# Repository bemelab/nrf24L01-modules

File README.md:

# nRF24L01+ modülleri — Elfatek

nRF24L01+ tabanlı RF modül tasarımları. Her proje kendi klasöründe, kendi README'si ve tasarım notlarıyla durur.

| Proje | Klasör | İçerik |
|---|---|---|
| **nRF24L01+ PA/LNA modülleri** | [`nrf24-pa-module/`](nrf24-pa-module) | 19 mm genişlikte, standart 2×4 pin dizilimli kartlar: NRF24PA, NRF24PL (RFX2401C PA/LNA), NRF24DN (PA'sız), NRF24DP (PA'lı, regülatörlü) |

Tasarımlar KiCad 9 ile, tablolardan Python betikleriyle üretilir. **Kartlar henüz test edilmedi.**

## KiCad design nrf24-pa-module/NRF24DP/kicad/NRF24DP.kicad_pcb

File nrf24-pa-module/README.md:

# nRF24L01+ PA/LNA modülleri — Elfatek

19 × 34 mm, 4 katmanlı, standart nRF24L01 2×4 pin dizilimli nRF24L01+ + RFX2401C PA/LNA modülleri.
Chip anten (Johanson 2450AT18A100E) ya da U.FL, montajda 0 Ω ile seçilir.

| Kart | Klasör | Harmonik filtre |
|---|---|---|
| **NRF24PA** rev A | kök (`docs/`, `kicad/`, `tools/`, `uretim/`) | Ayrık pi LC (C15–C19, L4, L5) |
| **NRF24PL** rev A | [`NRF24PL/`](NRF24PL) | Hazır seramik LPF, Johanson 2450LP14A100E (FL1) |
| **NRF24DN** rev A | [`NRF24DN/`](NRF24DN) | PA'sız minimal modül, hazır balun-filtre + AMS1117-3.3, 19 × 26 mm |
| **NRF24DP** rev A | [`NRF24DP/`](NRF24DP) | Hazır balun-filtre + LPF + AMS1117-3.3, 19 × 31.75 mm |

Ayrıntılar: [NRF24PA](docs/Tasarim%20notlari.md) · [NRF24PL](NRF24PL/docs/Tasarim%20notlari.md) ·
[NRF24DN](NRF24DN/docs/Tasarim%20notlari.md) · [NRF24DP](NRF24DP/docs/Tasarim%20notlari.md) tasarım notları

## Durum

ERC / DRC temiz, üretim dosyaları hazır. **Kartta henüz test edilmedi**: anten eşleştirme, harmonik
spektrumu ve kristal frekansı ölçülmeli (tasarım notlarında "Kartta doğrulanması gerekenler").

## Yeniden üretim

Şema ve PCB `tools/parts.py` (parça / net / konum) ve `tools/routes.py` (yollar) tablolarından üretilir.
KiCad 9 gerekir (`tools/build.py` içindeki yollar).

```
python tools/build.py            # NRF24PA
python NRF24PL/tools/build.py    # NRF24PL
python NRF24DN/tools/build.py    # NRF24DN
python NRF24DP/tools/build.py    # NRF24DP
```

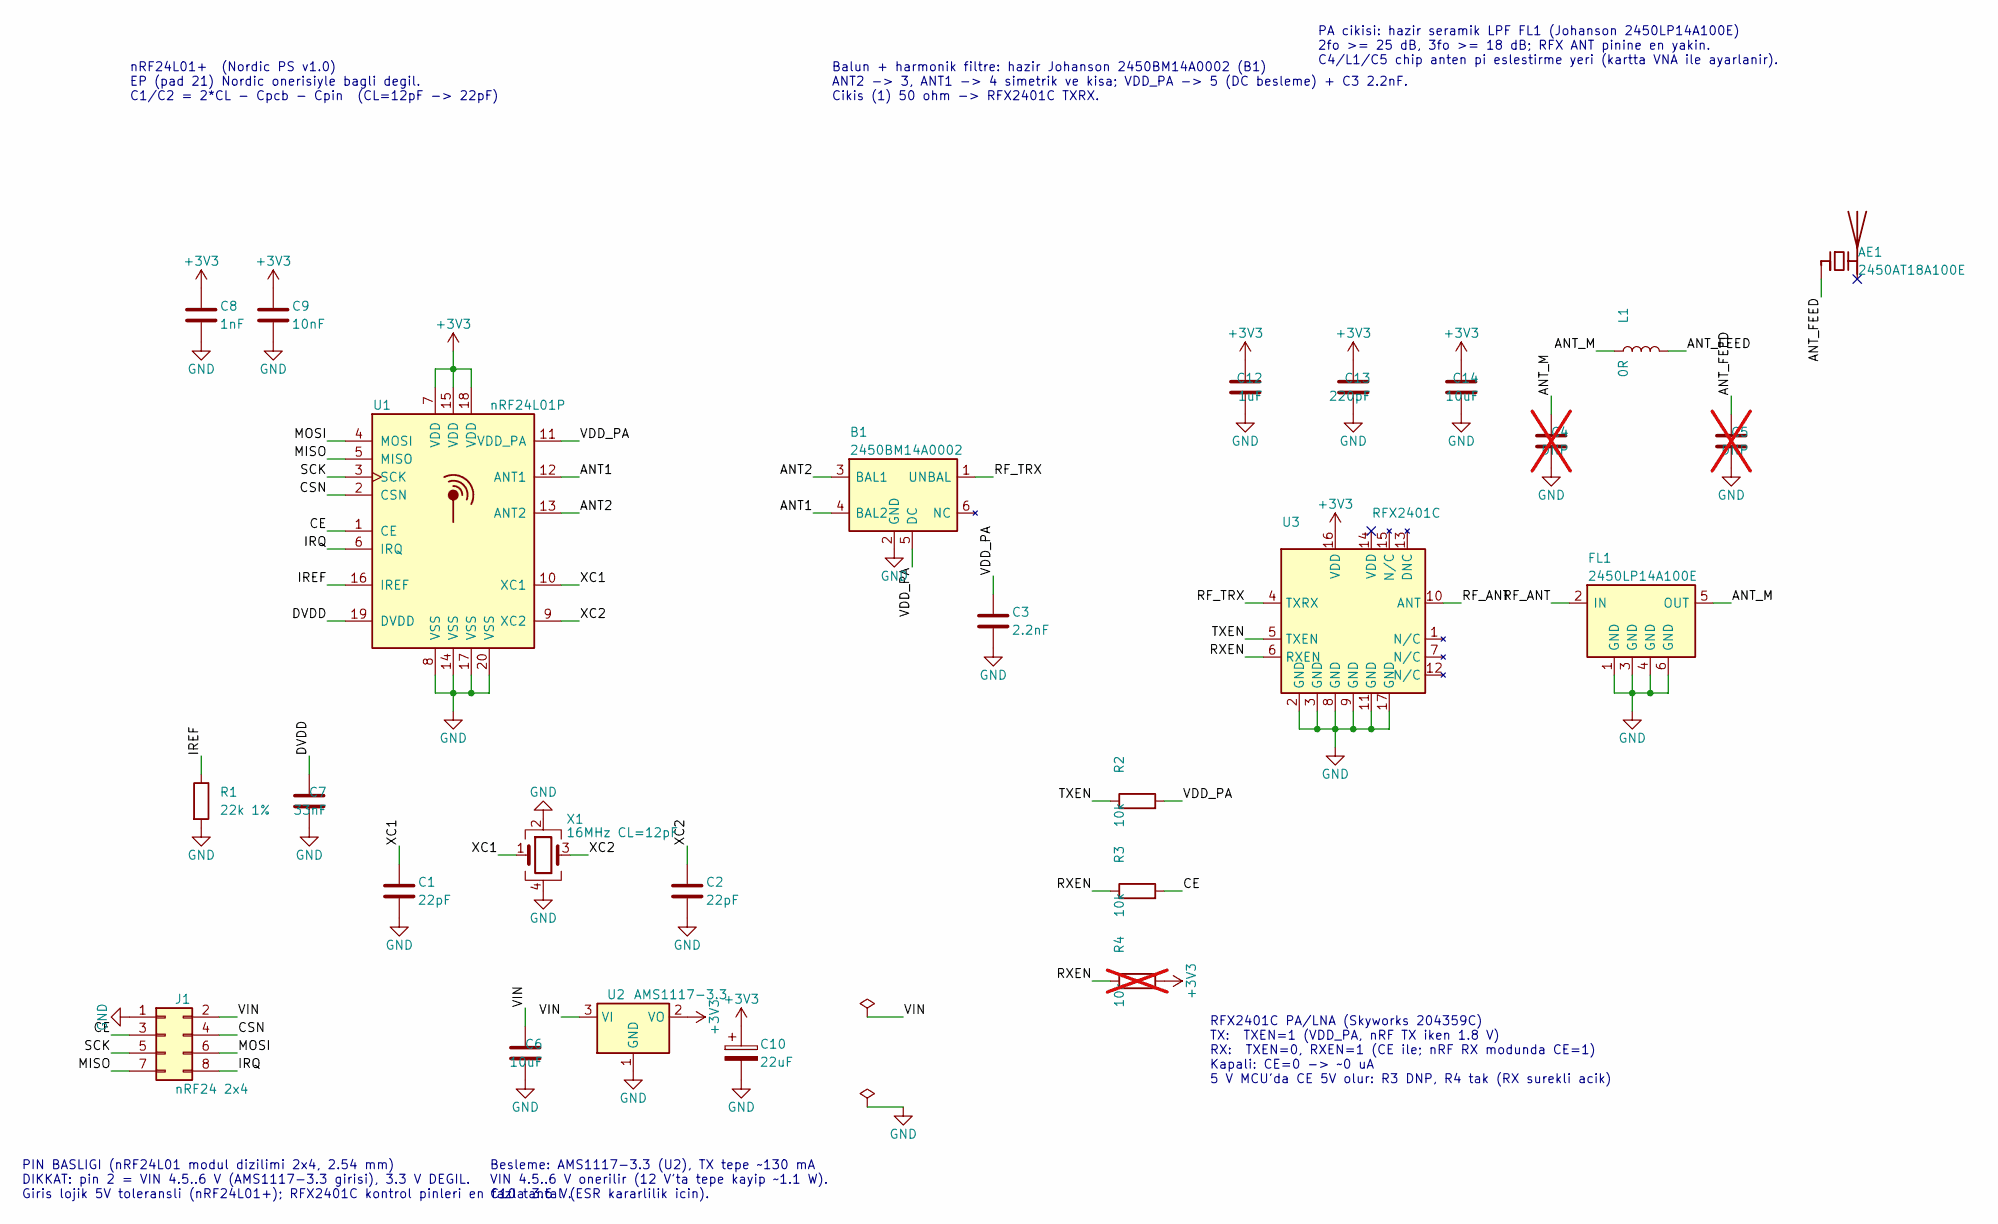
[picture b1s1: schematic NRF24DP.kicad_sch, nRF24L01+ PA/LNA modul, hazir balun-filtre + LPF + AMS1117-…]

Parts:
AE1: 2450AT18A100E; Johanson_2450AT18x100; MPN Johanson 2450AT18A100E
B1: 2450BM14A0002; Johanson_2450BM14_1.6x0.8mm; MPN Johanson 2450BM14A0002001T
C1, C2: 22pF; C_0402_1005Metric; MPN NP0 50V
C3: 2.2nF; C_0402_1005Metric; MPN X7R
C4, C5: DNP; C_0402_1005Metric; not fitted
C6: 10uF; C_0805_2012Metric; MPN X5R 25V
C7: 33nF; C_0402_1005Metric; MPN X7R
C8: 1nF; C_0402_1005Metric; MPN X7R
C9: 10nF; C_0402_1005Metric; MPN X7R
C10: 22uF; CP_EIA-3216-18_Kemet-A; MPN Tantal 22uF 10V A kilif
C12: 1uF; C_0402_1005Metric; MPN X5R 10V
C13: 220pF; C_0402_1005Metric; MPN NP0
C14: 10uF; C_0603_1608Metric; MPN X5R 10V
FL1: 2450LP14A100E; Johanson_2450LP14_1.6x0.8mm; MPN Johanson 2450LP14A100E
J1: nRF24 2x4; PinHeader_2x04_P2.54mm_Vertical
L1: 0R; L_0402_1005Metric
R1: 22k 1%; R_0402_1005Metric
R2, R3: 10k; R_0402_1005Metric
R4: 10k; R_0402_1005Metric; not fitted
U1: nRF24L01P; QFN-20-1EP_4x4mm_P0.5mm_EP2.5x2.5mm; MPN nRF24L01P-R
U2: AMS1117-3.3; SOT-223-3_TabPin2; MPN AMS1117-3.3 (AMS) / esdegeri
U3: RFX2401C; QFN-16-1EP_3x3mm_P0.5mm_EP1.7x1.7mm_ThermalVias; MPN RFX2401C (Skyworks) / AT2401C
X1: 16MHz CL=12pF; Crystal_SMD_3225-4Pin_3.2x2.5mm; MPN X322516MLB4SI (Yangxing) / esdegeri, +/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

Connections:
+3V3: C8.1, C9.1, C10.1, C12.2, C13.2, C14.2, R4.2, U1.7 (VDD), U1.15 (VDD), U1.18 (VDD), U2.2 (VO), U3.16 (VDD)
/ANT1: B1.4 (BAL2), U1.12 (ANT1)
/ANT2: B1.3 (BAL1), U1.13 (ANT2)
/ANT_FEED: AE1.1 (FEED), C5.2, L1.2
/ANT_M: C4.2, FL1.5 (OUT), L1.1
/CE: J1.3, R3.2, U1.1 (CE)
/CSN: J1.4, U1.2 (CSN)
/DVDD: C7.2, U1.19 (DVDD)
/IREF: R1.1, U1.16 (IREF)
/IRQ: J1.8, U1.6 (IRQ)
/MISO: J1.7, U1.5 (MISO)
/MOSI: J1.6, U1.4 (MOSI)
/RF_ANT: FL1.2 (IN), U3.10 (ANT)
/RF_TRX: B1.1 (UNBAL), U3.4 (TXRX)
/RXEN: R3.1, R4.1, U3.6 (RXEN)
/SCK: J1.5, U1.3 (SCK)
/TXEN: R2.1, U3.5 (TXEN)
/VDD_PA: B1.5 (DC), C3.1, R2.2, U1.11 (VDD_PA)
/VIN: C6.2, J1.2, U2.3 (VI)
/XC1: C1.1, U1.10 (XC1), X1.1
/XC2: C2.1, U1.9 (XC2), X1.3
GND: B1.2 (GND), C1.2, C2.2, C3.2, C4.1, C5.1, C6.1, C7.1, C8.2, C9.2, C10.2, C12.1, C13.1, C14.1, FL1.1 (GND), FL1.3 (GND), FL1.4 (GND), FL1.6 (GND), J1.1, R1.2, U1.8 (VSS), U1.14 (VSS), U1.17 (VSS), U1.20 (VSS), U2.1 (GND), U3.2 (GND), U3.3 (GND), U3.8 (GND), U3.9 (GND), U3.11 (GND), U3.17 (GND), X1.2, X1.4

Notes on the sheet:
PIN BASLIGI (nRF24L01 modul dizilimi 2x4, 2.54 mm) DIKKAT: pin 2 = VIN 4.5..6 V (AMS1117-3.3 girisi), 3.3 V DEGIL. Giris lojik 5V toleransli (nRF24L01+); RFX2401C kontrol pinleri en fazla 3.6 V.
nRF24L01+ (Nordic PS v1.0) EP (pad 21) Nordic onerisiyle bagli degil. C1/C2 = 2*CL - Cpcb - Cpin (CL=12pF -> 22pF)
Balun + harmonik filtre: hazir Johanson 2450BM14A0002 (B1) ANT2 -> 3, ANT1 -> 4 simetrik ve kisa; VDD_PA -> 5 (DC besleme) + C3 2.2nF. Cikis (1) 50 ohm -> RFX2401C TXRX.
RFX2401C PA/LNA (Skyworks 204359C) TX: TXEN=1 (VDD_PA, nRF TX iken 1.8 V) RX: TXEN=0, RXEN=1 (CE ile; nRF RX modunda CE=1) Kapali: CE=0 -> ~0 uA 5 V MCU'da CE 5V olur: R3 DNP, R4 tak (RX surekli acik)
PA cikisi: hazir seramik LPF FL1 (Johanson 2450LP14A100E) 2fo >= 25 dB, 3fo >= 18 dB; RFX ANT pinine en yakin. C4/L1/C5 chip anten pi eslestirme yeri (kartta VNA ile ayarlanir).
Besleme: AMS1117-3.3 (U2), TX tepe ~130 mA VIN 4.5..6 V onerilir (12 V'ta tepe kayip ~1.1 W). C10 tantal (ESR kararlilik icin).

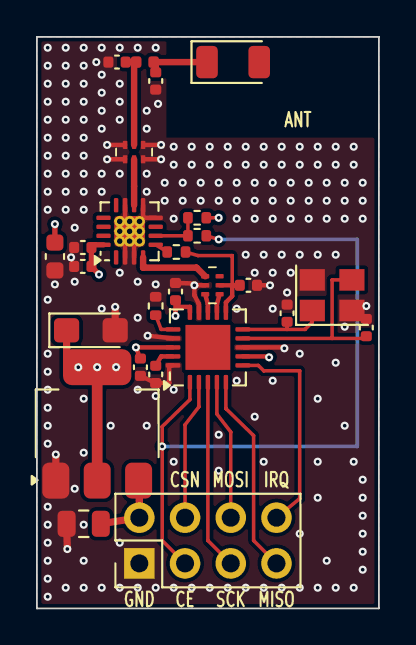
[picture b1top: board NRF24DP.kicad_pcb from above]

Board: 4 copper layers, 19.0 x 31.8 mm, 26 parts (0 on the bottom side), 22 nets.

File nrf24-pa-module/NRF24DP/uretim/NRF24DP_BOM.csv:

"Referans","Deger","Footprint","MPN","Adet","DNP"
"AE1","2450AT18A100E","RF_Antenna:Johanson_2450AT18x100","Johanson 2450AT18A100E","1",""
"B1","2450BM14A0002","elf_rf:Johanson_2450BM14_1.6x0.8mm","Johanson 2450BM14A0002001T","1",""
"C1,C2","22pF","Capacitor_SMD:C_0402_1005Metric","NP0 50V","2",""
"C3","2.2nF","Capacitor_SMD:C_0402_1005Metric","X7R","1",""
"C4,C5","DNP","Capacitor_SMD:C_0402_1005Metric","","2","Yerleştirilmemeli"
"C6","10uF","Capacitor_SMD:C_0805_2012Metric","X5R 25V","1",""
"C7","33nF","Capacitor_SMD:C_0402_1005Metric","X7R","1",""
"C8","1nF","Capacitor_SMD:C_0402_1005Metric","X7R","1",""
"C9","10nF","Capacitor_SMD:C_0402_1005Metric","X7R","1",""
"C10","22uF","Capacitor_Tantalum_SMD:CP_EIA-3216-18_Kemet-A","Tantal 22uF 10V A kilif","1",""
"C12","1uF","Capacitor_SMD:C_0402_1005Metric","X5R 10V","1",""
"C13","220pF","Capacitor_SMD:C_0402_1005Metric","NP0","1",""
"C14","10uF","Capacitor_SMD:C_0603_1608Metric","X5R 10V","1",""
"FL1","2450LP14A100E","elf_rf:Johanson_2450LP14_1.6x0.8mm","Johanson 2450LP14A100E","1",""
"J1","nRF24 2x4","Connector_PinHeader_2.54mm:PinHeader_2x04_P2.54mm_Vertical","","1",""
"L1","0R","Inductor_SMD:L_0402_1005Metric","","1",""
"R1","22k 1%","Resistor_SMD:R_0402_1005Metric","","1",""
"R2,R3","10k","Resistor_SMD:R_0402_1005Metric","","2",""
"R4","10k","Resistor_SMD:R_0402_1005Metric","","1","Yerleştirilmemeli"
"U1","nRF24L01P","Package_DFN_QFN:QFN-20-1EP_4x4mm_P0.5mm_EP2.5x2.5mm","nRF24L01P-R","1",""
"U2","AMS1117-3.3","Package_TO_SOT_SMD:SOT-223-3_TabPin2","AMS1117-3.3 (AMS) / esdegeri","1",""
"U3","RFX2401C","Package_DFN_QFN:QFN-16-1EP_3x3mm_P0.5mm_EP1.7x1.7mm_ThermalVias","RFX2401C (Skyworks) / AT2401C","1",""
"X1","16MHz CL=12pF","Crystal:Crystal_SMD_3225-4Pin_3.2x2.5mm","X322516MLB4SI (Yangxing) / esdegeri, +/-20ppm","1",""
